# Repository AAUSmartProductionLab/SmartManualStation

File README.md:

# Smart Manual Station overview
 The Smart Manual Station is a project developed at Aalborg University as a smart digital aid for the worker at a manual station. The station consists of:

  * Table on wheels 
  * Raspberry pi as the "brain"
  * Pick By Light setup
  * OPC-UA server
  * Simple GUI

further future features includes:
  * mqtt support
  * Storage database of pick by light setup
  * Implementation of RFID-scanner
  * Webinterface
  
 # The station itself

 # Graphical Unser Interface 
The graphical userinterface is build with [PySimpleGui](https://pysimplegui.readthedocs.io/en/latest/)  

 # PCB breakout box
Added as a git subtree to this repository. Dedicated upstream repo can be found [here](https://github.com/hjalte33/rpi-pcb)

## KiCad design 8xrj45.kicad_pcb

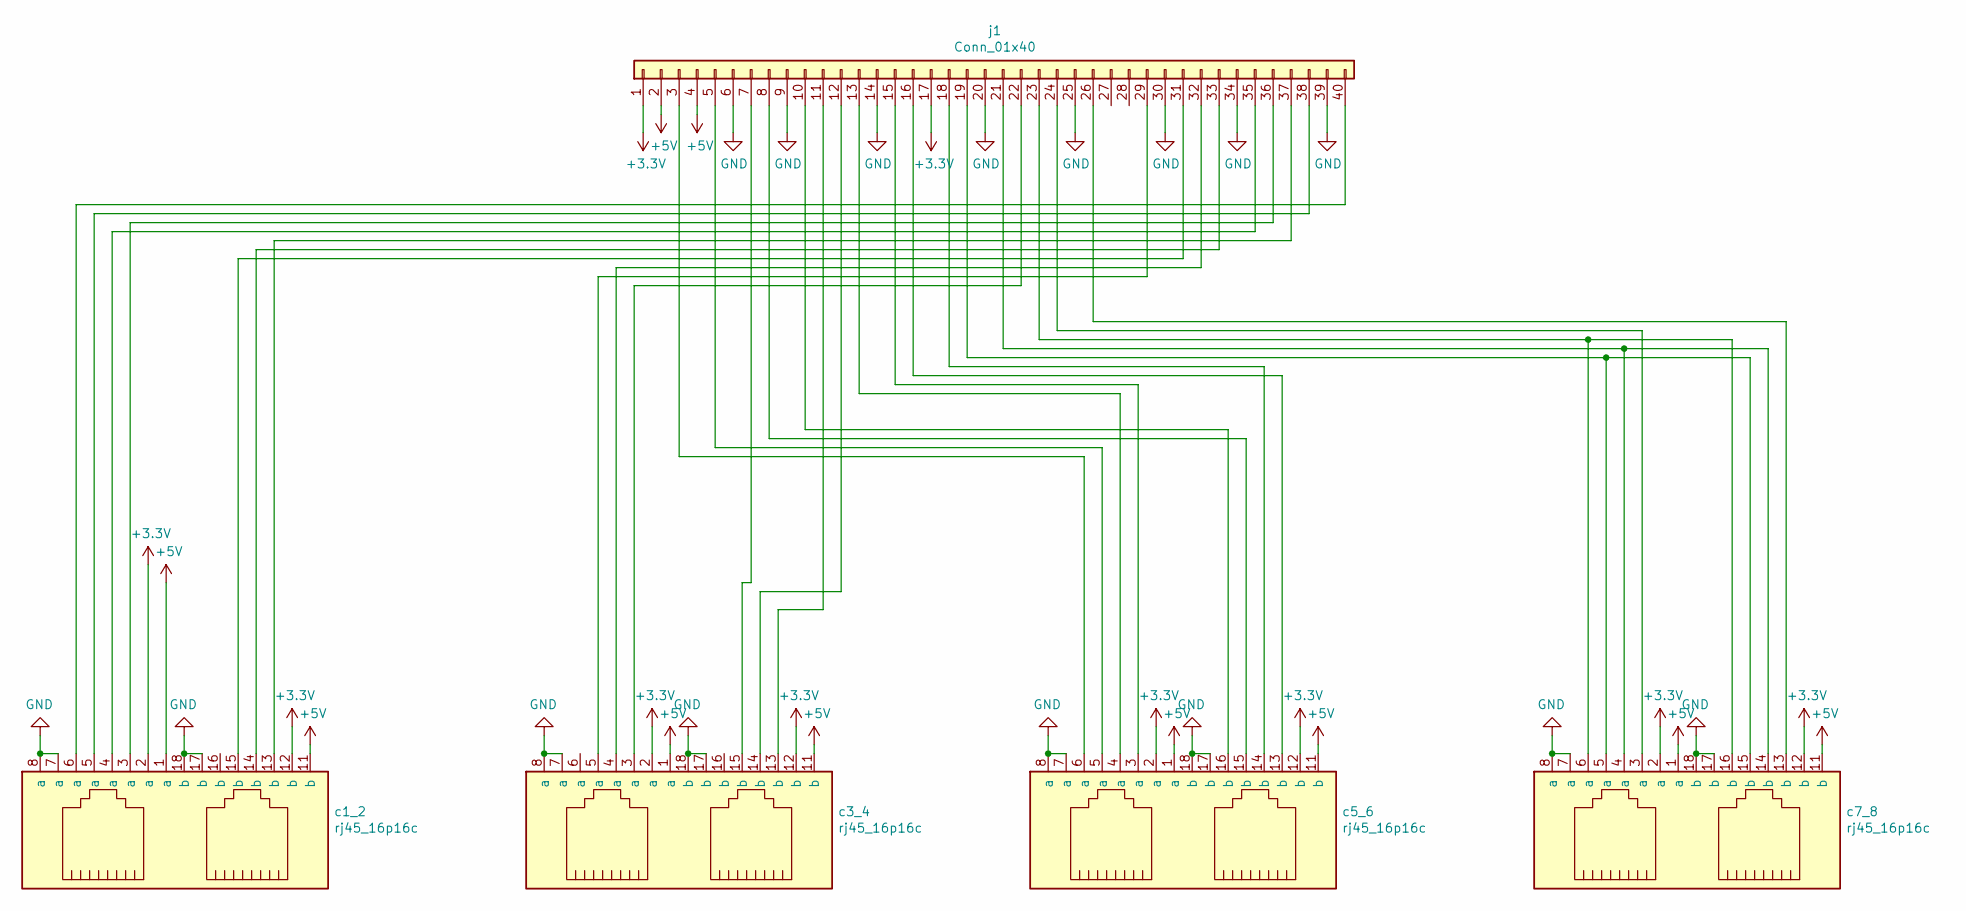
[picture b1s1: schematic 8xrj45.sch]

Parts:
c1_2, c3_4, c5_6, c7_8: rj45_16p16c; 2xrj45_connector
j1: Conn_01x40; IDC-Header_2x20_P2.54mm_Vertical

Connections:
+3V3: c1_2.2 (a), c1_2.12 (b), c3_4.2 (a), c3_4.12 (b), c5_6.2 (a), c5_6.12 (b), c7_8.2 (a), c7_8.12 (b), j1.1, j1.17
+5V: c1_2.1 (a), c1_2.11 (b), c3_4.1 (a), c3_4.11 (b), c5_6.1 (a), c5_6.11 (b), c7_8.1 (a), c7_8.11 (b), j1.2, j1.4
GND: c1_2.7 (a), c1_2.8 (a), c1_2.17 (b), c1_2.18 (b), c3_4.7 (a), c3_4.8 (a), c3_4.17 (b), c3_4.18 (b), c5_6.7 (a), c5_6.8 (a), c5_6.17 (b), c5_6.18 (b), c7_8.7 (a), c7_8.8 (a), c7_8.17 (b), c7_8.18 (b), j1.6, j1.9, j1.14, j1.20, j1.25, j1.30, j1.34, j1.39
unnamed: c1_2.3 (a), j1.36
unnamed: c1_2.4 (a), j1.35
unnamed: c1_2.5 (a), j1.38
unnamed: c1_2.6 (a), j1.40
unnamed: c1_2.13 (b), j1.37
unnamed: c1_2.14 (b), j1.33
unnamed: c1_2.15 (b), j1.31
unnamed: c3_4.3 (a), j1.22
unnamed: c3_4.4 (a), j1.32
unnamed: c3_4.5 (a), j1.29
unnamed: c3_4.13 (b), j1.11
unnamed: c3_4.14 (b), j1.12
unnamed: c3_4.15 (b), j1.7
unnamed: c5_6.3 (a), j1.15
unnamed: c5_6.4 (a), j1.13
unnamed: c5_6.5 (a), j1.5
unnamed: c5_6.6 (a), j1.3
unnamed: c5_6.13 (b), j1.16
unnamed: c5_6.14 (b), j1.18
unnamed: c5_6.15 (b), j1.8
unnamed: c5_6.16 (b), j1.10
unnamed: c7_8.3 (a), j1.24
unnamed: c7_8.13 (b), j1.26
unnamed: c7_8.4 (a), c7_8.14 (b), j1.21
unnamed: c7_8.5 (a), c7_8.15 (b), j1.19
unnamed: c7_8.6 (a), c7_8.16 (b), j1.23

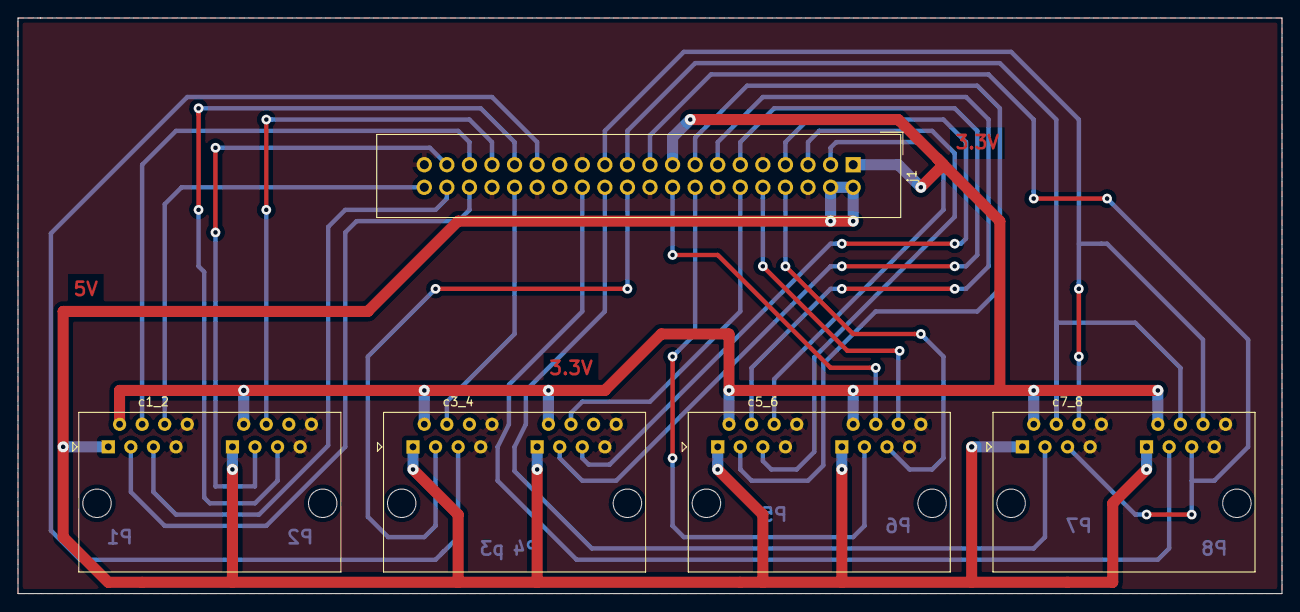
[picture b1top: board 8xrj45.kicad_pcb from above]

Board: 2 copper layers, 142.2 x 64.8 mm, 5 parts (0 on the bottom side), 29 nets.

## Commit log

2020-09-09 v2 design
2020-09-09 cleanup
2020-09-14 no idea what changed
2020-09-21 fresh export
2020-10-05 initial commit of new code base.
2020-10-12 working commit. add dimming effect + gui and more
2020-10-13 Logging and working OPCUA server + minor fixes
2020-10-21 first commit for festo_connect.py
2020-11-03 lots of gui elements and content map features
2020-11-03 disabled dummy pick thread
2020-11-03 quick readme file
2020-11-04 overall gui design finished.
2020-11-10 moving files aronud
2020-11-10 moving files around
2020-11-11 fix major racecondition bug blocking writes
2020-11-11 turn on the display when something happens on pbl
2020-11-11 cleanup and small bug fixes.
2020-11-11 window titles
2020-11-11 fix:indentation error
2020-11-11 fix:start.desktop file logo
2020-11-13 move aux origin
2020-11-13 cleanup and doc preperation
2020-11-13 deleted files listed in .gitignore
2020-11-13 pinout documentation added
2020-11-13 fix: pin 5 and 6 are not connected
2020-11-13 documentation and cad
2020-11-13 add: lasercut files
2020-11-16 adding pictures and testing size
2020-11-16 added more images to readme
2020-11-16 fix: image path and spacing
2020-11-19 add:pictures
2020-11-19 initial
2020-11-23 removal of unnessesary code
2020-11-23 bugfix: path not file when loading images
2020-11-23 documentation
2020-12-14 compleatly rewritten for new pic by light api
2020-12-14 add work_finished tag to port state
2020-12-14 use work_finished() on pbl when submitting work.
2020-12-15 add: festo connect
2020-12-15 bugfixes
2020-12-15 add dummy festo object: orderDescription
2021-02-16 Festo connect fix (#3)
    * compleatly rewritten for new pic by light api
    * add work_finished tag to port state
    * use work_finished() on pbl when submitting work.
    * add: festo connect
    * bugfixes
    * add dummy festo object: orderDescription
2021-02-16 select and deselect by content name
2021-02-16 select by content and rework of commands
2021-02-18 renaming items for easier understanding
2021-02-18 select and deselect content now returs port_number
2021-02-18 adapted to use select_conten() instead
2021-02-18 spelling error
2021-03-04 grammer
2021-03-04 Select by item (#4)
    * select and deselect by content name
    * renaming items for easier understanding
    * select and deselect content now returns resulting port_number
    * adapted festo connect to use select_conten() instead
2021-03-15 adde launch argument to enable festo connect
2021-03-22 added select result tag to opcua server
2021-03-22 name change
2021-03-22 Select by content opcua feedback (#6)
    * add launch argument to enable festo connect
    * added select result tag to opcua server
    * name change
2021-03-22 adde launch argument to enable festo connect (#5)
